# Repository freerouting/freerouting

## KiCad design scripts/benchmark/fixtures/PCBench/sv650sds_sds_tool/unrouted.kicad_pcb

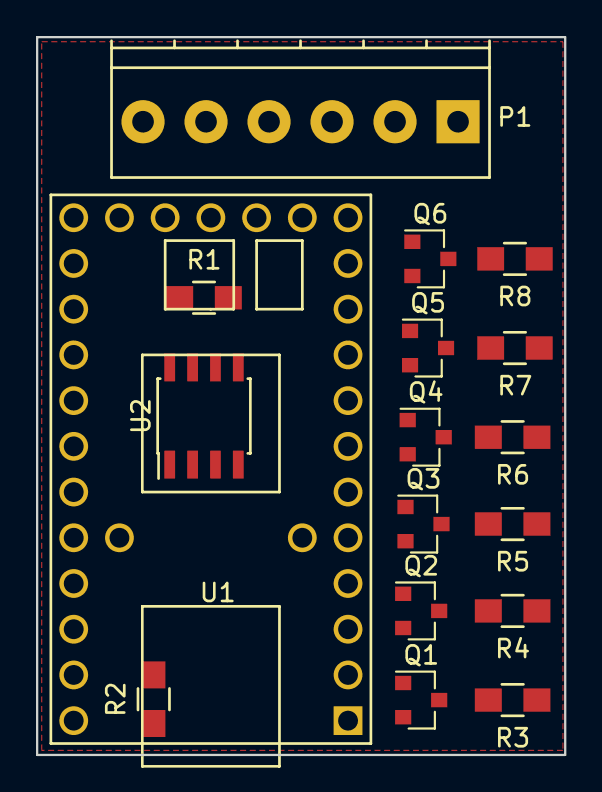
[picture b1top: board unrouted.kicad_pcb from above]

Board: 2 copper layers, 29.3 x 39.9 mm, 17 parts (0 on the bottom side), 21 nets, no tracks yet.

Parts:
P1: CONN_01X06; TerminalBlock_Pheonix_PT-3.5mm_6pol
Q1, Q2, Q3, Q4, Q5, Q6: MMBT3904; SOT-23
R1: 510; R_0805_HandSoldering
R2: 1k; R_0805_HandSoldering
R3: 560; R_0805_HandSoldering
R4: 630; R_0805_HandSoldering
R5: 1.5k; R_0805_HandSoldering
R6: 2.7k; R_0805_HandSoldering
R7: 6.8k; R_0805_HandSoldering
R8: 15k; R_0805_HandSoldering
U1: Teensy2.0
U2: STl9637; SOIC-8_3.9x4.9mm_Pitch1.27mm

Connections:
+5V: R2.1, U1.29, U2.3
+12V: P1.6, R1.1, U2.7
ECU_GPS: P1.2, R3.1, R4.1, R5.1, R6.1, R7.1, R8.1
GND: P1.1, Q1.2, Q2.2, Q3.2, Q4.2, Q5.2, Q6.2, U1.1, U1.15, U2.5
GPS: P1.3, R2.2, U1.28
Gear1: Q1.1, U1.2
Gear2: Q2.1, U1.3
Gear3: Q3.1, U1.4
Gear4: Q4.1, U1.5
Gear5: Q5.1, U1.6
Gear6: Q6.1, U1.7
K_LINE: P1.4, R1.2, U2.6
unnamed: Q1.3, R3.2
unnamed: Q2.3, R4.2
unnamed: Q3.3, R5.2
unnamed: Q4.3, R6.2
unnamed: Q5.3, R7.2
unnamed: Q6.3, R8.2
OUTPUT: P1.5, U1.19
TTL_K_RX: U1.9, U2.1
TTL_K_TX: U1.10, U2.4

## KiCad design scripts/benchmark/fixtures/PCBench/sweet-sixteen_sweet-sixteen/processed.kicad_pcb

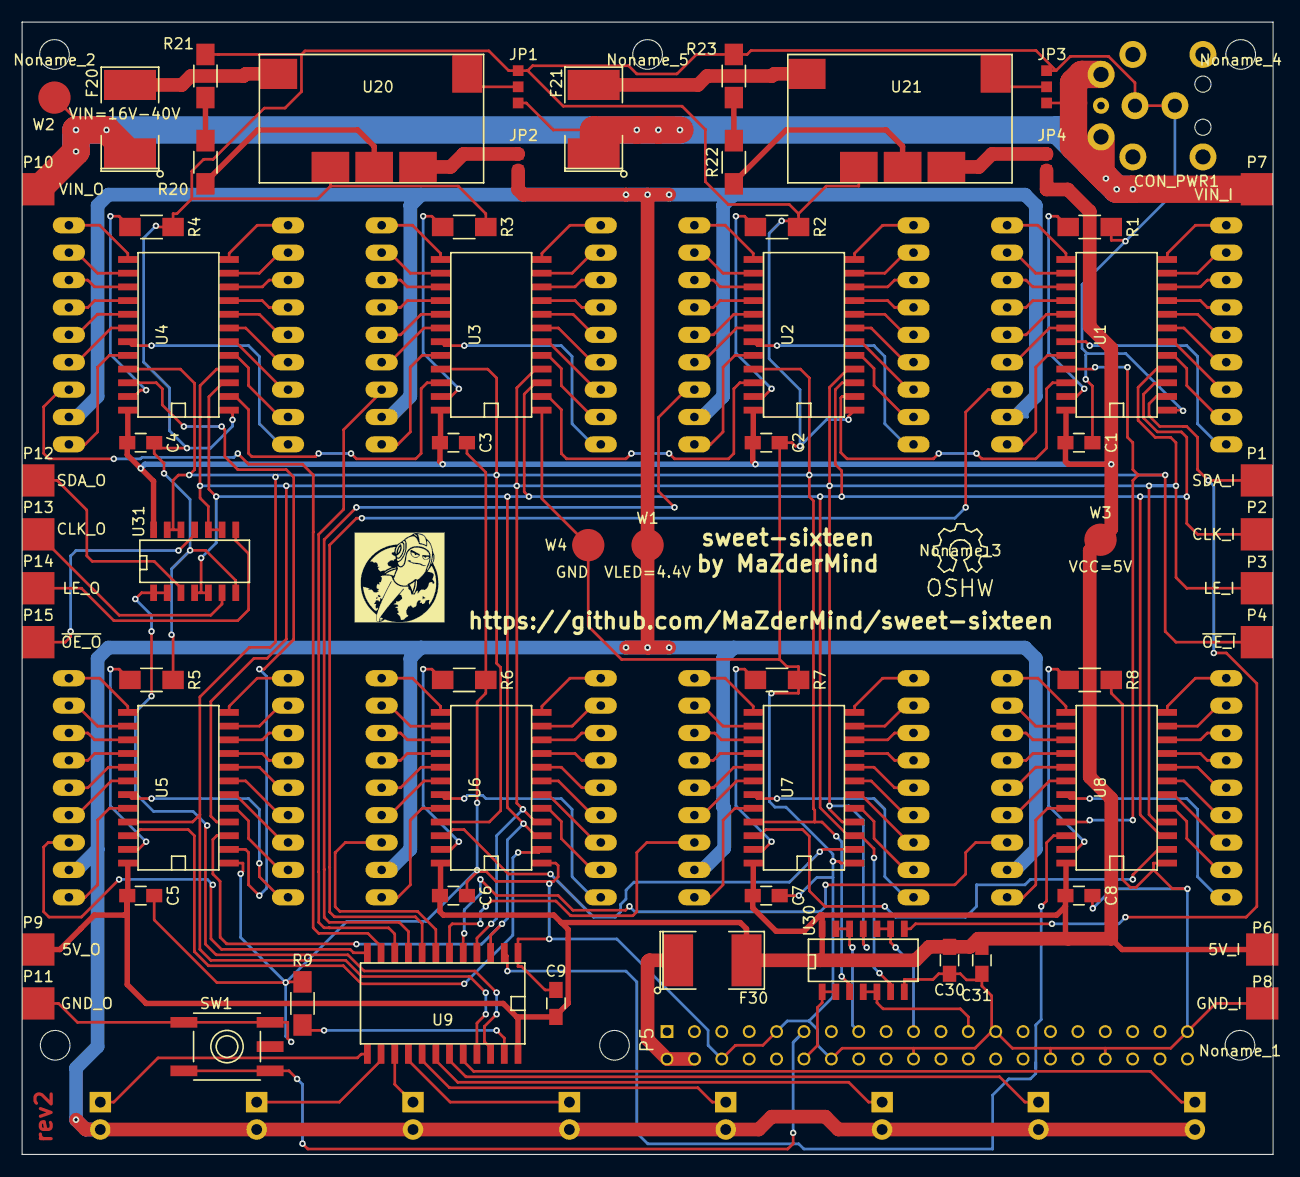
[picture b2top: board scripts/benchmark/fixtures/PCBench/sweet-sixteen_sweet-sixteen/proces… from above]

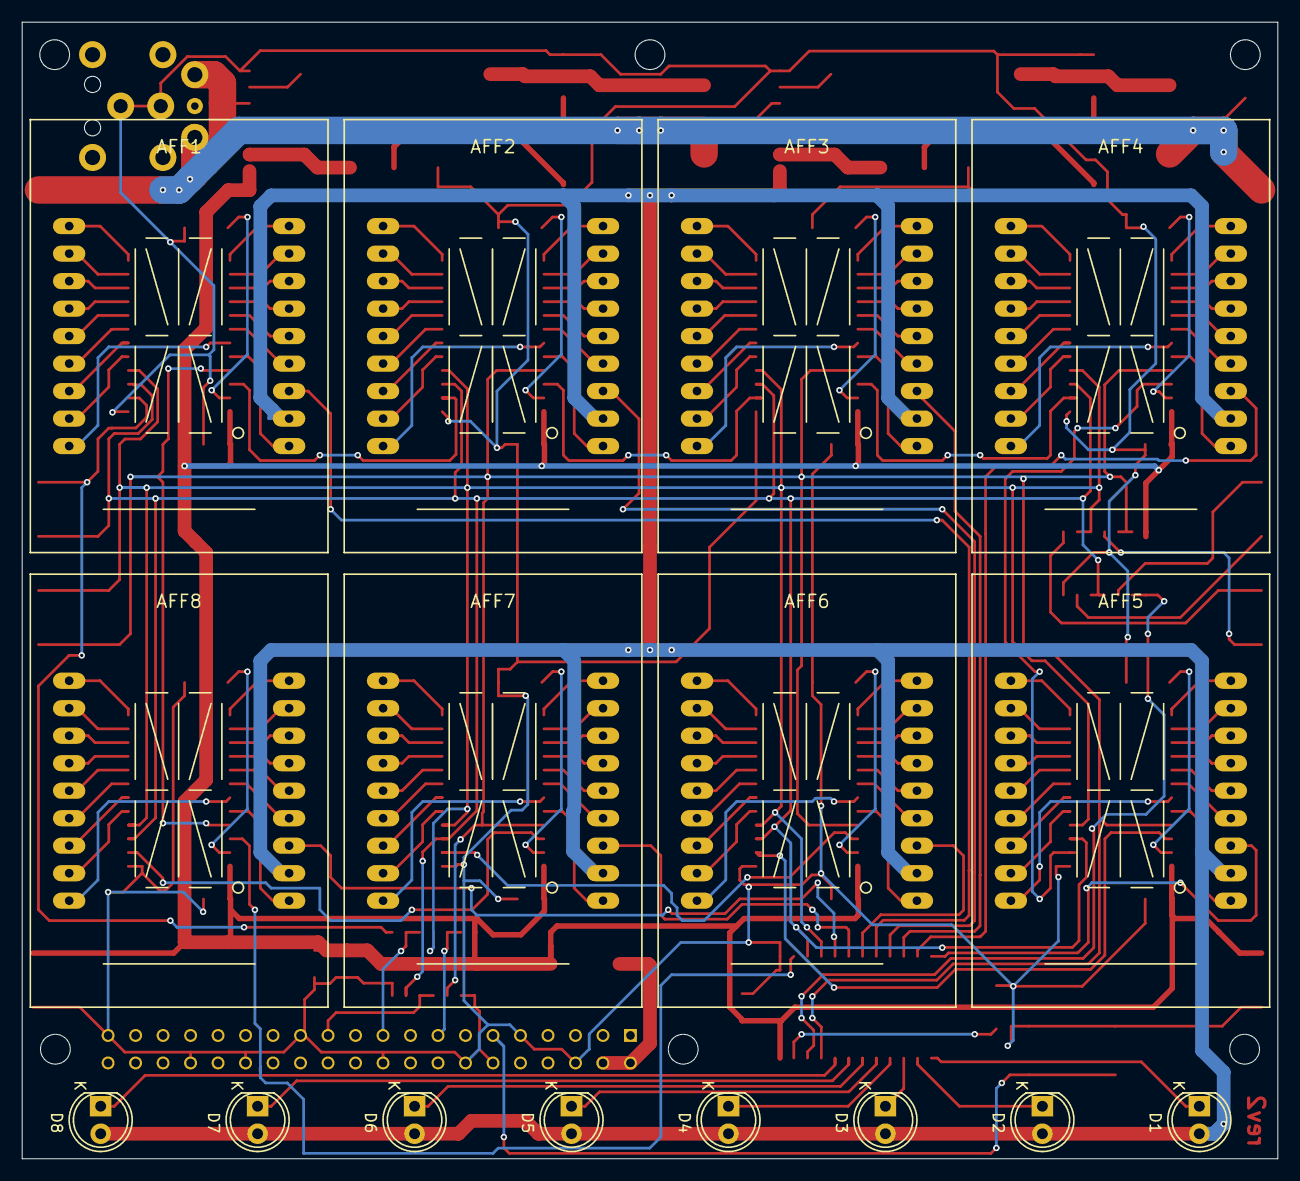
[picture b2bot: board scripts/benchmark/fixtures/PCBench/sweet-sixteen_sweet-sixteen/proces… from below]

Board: 2 copper layers, 116.0 x 105.0 mm, 86 parts (16 on the bottom side), 190 nets.

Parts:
AFF1, AFF2, AFF3, AFF4, AFF5, AFF6, AFF7, AFF8: 16SEGMENTS; PSA12-11
C1, C2, C3, C4, C5, C6, C7, C8, C9, C30, C31: 0.1μF; C_0805_HandSoldering
CON_PWR1: PWR; DELL-PCON
D1, D2, D3, D4, D5, D6, D7, D8: LED; LED-5MM
F20, F21: 1.2A F; SMD-2112_Pol
F30: 2.5A S; SMD-2112_Pol
JP1, JP3: JUMPER3; SMD_Jumper_3
JP2, JP4: JUMPER; SMD_Jumper_2
Noname_1, Noname_2, Noname_4, Noname_5: M2.5; m25-mounting-hole
Noname_3: Symbol_OSHW-Logo_SilkScreen
P1: SDA_I; Measurement_Point_Square-SMD-Pad_Big
P2: CLK_I; Measurement_Point_Square-SMD-Pad_Big
P3: LE_I; Measurement_Point_Square-SMD-Pad_Big
P4: ~OE_I; Measurement_Point_Square-SMD-Pad_Big
P5: CONN_02X20; rpi-header
P6: 5V_I; Measurement_Point_Square-SMD-Pad_Big
P7: VIN_I; Measurement_Point_Square-SMD-Pad_Big
P8: GND_I; Measurement_Point_Square-SMD-Pad_Big
P9: 5V_O; Measurement_Point_Square-SMD-Pad_Big
P10: VIN_O; Measurement_Point_Square-SMD-Pad_Big
P11: GND_O; Measurement_Point_Square-SMD-Pad_Big
P12: SDA_O; Measurement_Point_Square-SMD-Pad_Big
P13: CLK_O; Measurement_Point_Square-SMD-Pad_Big
P14: LE_O; Measurement_Point_Square-SMD-Pad_Big
P15: ~OE_O; Measurement_Point_Square-SMD-Pad_Big
R1, R2, R3, R4, R5, R6, R7, R8, R9: 1k; R_1206_HandSoldering
R20, R22: 1.2k; R_1206_HandSoldering
R21: 680; R_1206_HandSoldering
R23: 270; R_1206_HandSoldering
SW1: SW_PUSH; ADTSM61
U1, U2, U3, U4, U5, U6, U7, U8, U9: STP16CPC26; STP16CPC26MTR
U20, U21: OKI-T/3-W40; OKI-T3
U30, U31: 74HCT08; SN74HCT08D
W1: VLED=4.4V; Measurement_Point_Round-SMD-Pad_Big
W2: VIN=16V-40V; Measurement_Point_Round-SMD-Pad_Big
W3: VCC=5V; Measurement_Point_Round-SMD-Pad_Big
W4: GND; Measurement_Point_Round-SMD-Pad_Big

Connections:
/CLK: P2.1, U1.3, U2.3, U3.3, U4.3, U5.3, U6.3, U7.3, U8.3, U9.3, U30.6, U31.4, U31.5
/CLK_O: P13.1, U31.6
/LE: P3.1, U1.4, U2.4, U3.4, U4.4, U5.4, U6.4, U7.4, U8.4, U9.4, U30.11, U31.9, U31.10
/LE_O: P14.1, U31.8
/PI_CLK: P5.23, U30.4, U30.5
/PI_LE: P5.15, U30.12, U30.13
/PI_SDA: P5.19, U30.9, U30.10
/SDA_9O: U9.22, U31.1, U31.2
/SDA_12: U1.22, U2.2
/SDA_34: U3.22, U4.2
/SDA_45: U4.22, U5.2
/SDA_56: U5.22, U6.2
/SDA_67: U6.22, U7.2
/SDA_78: U7.22, U8.2
/SDA_89: U8.22, U9.2
/SDA_I: P1.1, U1.2, U30.8
/SDA_O: P12.1, U31.3
/SD_23: U2.22, U3.2
/VLED: AFF1.11, AFF2.11, AFF3.11, AFF4.11, AFF5.11, AFF6.11, AFF7.11, AFF8.11, D1.2, D2.2, D3.2, D4.2, D5.2, D6.2, D7.2, D8.2, JP2.2, W1.1
/V_PI: F30.1, P5.2, P5.4
/~OE: P4.1, U1.21, U2.21, U3.21, U4.21, U5.21, U6.21, U7.21, U8.21, U9.21, U30.3, U31.12, U31.13
/~OE_O: P15.1, U31.11
/~PI_OE: P5.12, U30.1, U30.2
GND: C1.2, C2.2, C3.2, C4.2, C5.2, C6.2, C7.2, C8.2, C9.2, C30.2, C31.2, CON_PWR1.2, JP1.1, JP3.1, P5.6, P5.9, P5.14, P5.20, P5.25, P5.30, P5.34, P5.39, P8.1, P11.1, R1.1, R2.1, R3.1, R4.1, R5.1, R6.1, R7.1, R8.1, R9.1, R21.2, R23.2, SW1.1, U1.1, U2.1, U3.1, U4.1, U5.1, U6.1, U7.1, U8.1, U9.1, U20.3, U21.3, U30.7, U31.7, W4.1
unnamed: AFF1.1, U1.12
unnamed: AFF1.2, U1.11
unnamed: AFF1.3, U1.10
unnamed: AFF1.4, U1.9
unnamed: AFF1.5, U1.8
unnamed: AFF1.6, U1.7
unnamed: AFF1.7, U1.6
unnamed: AFF1.8, U1.5
unnamed: AFF1.9, U1.19
unnamed: AFF1.10, U1.20
unnamed: AFF1.12, U9.8
unnamed: AFF1.13, U1.18
unnamed: AFF1.14, U1.17
unnamed: AFF1.15, U1.16
unnamed: AFF1.16, U1.15
unnamed: AFF1.17, U1.14
unnamed: AFF1.18, U1.13
unnamed: AFF2.1, U2.12
unnamed: AFF2.2, U2.11
unnamed: AFF2.3, U2.10
unnamed: AFF2.4, U2.9
unnamed: AFF2.5, U2.8
unnamed: AFF2.6, U2.7
unnamed: AFF2.7, U2.6
unnamed: AFF2.8, U2.5
unnamed: AFF2.9, U2.19
unnamed: AFF2.10, U2.20
unnamed: AFF2.12, U9.9
unnamed: AFF2.13, U2.18
unnamed: AFF2.14, U2.17
unnamed: AFF2.15, U2.16
unnamed: AFF2.16, U2.15
unnamed: AFF2.17, U2.14
unnamed: AFF2.18, U2.13
unnamed: AFF3.1, U3.12
unnamed: AFF3.2, U3.11
unnamed: AFF3.3, U3.10
unnamed: AFF3.4, U3.9
unnamed: AFF3.5, U3.8
unnamed: AFF3.6, U3.7
unnamed: AFF3.7, U3.6
unnamed: AFF3.8, U3.5
unnamed: AFF3.9, U3.19
unnamed: AFF3.10, U3.20
unnamed: AFF3.12, U9.10
unnamed: AFF3.13, U3.18
unnamed: AFF3.14, U3.17
unnamed: AFF3.15, U3.16
unnamed: AFF3.16, U3.15
unnamed: AFF3.17, U3.14
unnamed: AFF3.18, U3.13
unnamed: AFF4.1, U4.12
unnamed: AFF4.2, U4.11
unnamed: AFF4.3, U4.10
unnamed: AFF4.4, U4.9
unnamed: AFF4.5, U4.8
unnamed: AFF4.6, U4.7
unnamed: AFF4.7, U4.6
unnamed: AFF4.8, U4.5
unnamed: AFF4.9, U4.19
unnamed: AFF4.10, U4.20
unnamed: AFF4.12, U9.11
unnamed: AFF4.13, U4.18
unnamed: AFF4.14, U4.17
unnamed: AFF4.15, U4.16
unnamed: AFF4.16, U4.15
unnamed: AFF4.17, U4.14
unnamed: AFF4.18, U4.13
unnamed: AFF5.1, U5.12
unnamed: AFF5.2, U5.11
unnamed: AFF5.3, U5.10
unnamed: AFF5.4, U5.9
unnamed: AFF5.5, U5.8
unnamed: AFF5.6, U5.7
unnamed: AFF5.7, U5.6
unnamed: AFF5.8, U5.5
unnamed: AFF5.9, U5.19
unnamed: AFF5.10, U5.20
unnamed: AFF5.12, U9.12
unnamed: AFF5.13, U5.18
unnamed: AFF5.14, U5.17
unnamed: AFF5.15, U5.16
unnamed: AFF5.16, U5.15
unnamed: AFF5.17, U5.14
unnamed: AFF5.18, U5.13
unnamed: AFF6.1, U6.12
unnamed: AFF6.2, U6.11
unnamed: AFF6.3, U6.10
unnamed: AFF6.4, U6.9
unnamed: AFF6.5, U6.8
unnamed: AFF6.6, U6.7
unnamed: AFF6.7, U6.6
unnamed: AFF6.8, U6.5
unnamed: AFF6.9, U6.19
unnamed: AFF6.10, U6.20
unnamed: AFF6.12, U9.7
unnamed: AFF6.13, U6.18
unnamed: AFF6.14, U6.17
unnamed: AFF6.15, U6.16
unnamed: AFF6.16, U6.15
unnamed: AFF6.17, U6.14
unnamed: AFF6.18, U6.13
unnamed: AFF7.1, U7.12
unnamed: AFF7.2, U7.11
unnamed: AFF7.3, U7.10
unnamed: AFF7.4, U7.9
unnamed: AFF7.5, U7.8
unnamed: AFF7.6, U7.7
unnamed: AFF7.7, U7.6
unnamed: AFF7.8, U7.5
unnamed: AFF7.9, U7.19
unnamed: AFF7.10, U7.20
unnamed: AFF7.12, U9.6
unnamed: AFF7.13, U7.18
unnamed: AFF7.14, U7.17
unnamed: AFF7.15, U7.16
unnamed: AFF7.16, U7.15
unnamed: AFF7.17, U7.14
unnamed: AFF7.18, U7.13
unnamed: AFF8.1, U8.12
unnamed: AFF8.2, U8.11
unnamed: AFF8.3, U8.10
unnamed: AFF8.4, U8.9
unnamed: AFF8.5, U8.8
unnamed: AFF8.6, U8.7
unnamed: AFF8.7, U8.6
unnamed: AFF8.8, U8.5
unnamed: AFF8.9, U8.19
unnamed: AFF8.10, U8.20
unnamed: AFF8.12, U9.5
unnamed: AFF8.13, U8.18
unnamed: AFF8.14, U8.17
unnamed: AFF8.15, U8.16
unnamed: AFF8.16, U8.15
unnamed: AFF8.17, U8.14
unnamed: AFF8.18, U8.13
unnamed: D1.1, U9.13
unnamed: D2.1, U9.14
unnamed: D3.1, U9.15
unnamed: D4.1, U9.16
unnamed: D5.1, U9.17
unnamed: D6.1, U9.18
unnamed: D7.1, U9.19
unnamed: D8.1, U9.20
unnamed: F20.2, U20.2
unnamed: F21.2, U21.2
unnamed: JP1.2, U20.1
unnamed: JP2.1, U20.5
unnamed: JP3.2, U21.1
unnamed: JP4.1, U21.5
unnamed: P5.11, SW1.2
unnamed: R1.2, U1.23
unnamed: R2.2, U2.23
unnamed: R3.2, U3.23
unnamed: R4.2, U4.23
unnamed: R5.2, U5.23
unnamed: R6.2, U6.23
unnamed: R7.2, U7.23
unnamed: R8.2, U8.23
unnamed: R9.2, U9.23
unnamed: R20.1, R21.1
unnamed: R20.2, U20.4
unnamed: R22.1, R23.1
unnamed: R22.2, U21.4
VCC: C1.1, C2.1, C3.1, C4.1, C5.1, C6.1, C7.1, C8.1, C9.1, C30.1, C31.1, F30.2, JP4.2, P6.1, P9.1, U1.24, U2.24, U3.24, U4.24, U5.24, U6.24, U7.24, U8.24, U9.24, U30.14, U31.14, W3.1
VIN: CON_PWR1.1, F20.1, F21.1, JP1.3, JP3.3, P7.1, P10.1, W2.1

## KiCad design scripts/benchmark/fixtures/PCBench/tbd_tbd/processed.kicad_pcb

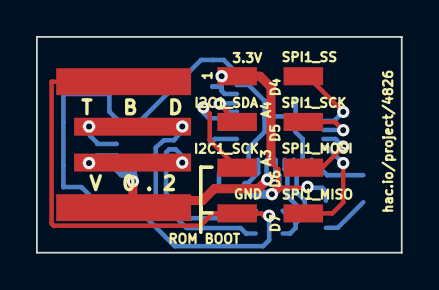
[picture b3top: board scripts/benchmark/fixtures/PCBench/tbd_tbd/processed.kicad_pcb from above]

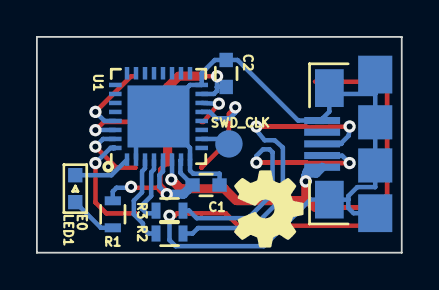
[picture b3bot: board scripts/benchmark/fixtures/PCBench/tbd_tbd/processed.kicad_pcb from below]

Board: 2 copper layers, 20.3 x 12.0 mm, 11 parts (9 on the bottom side), 16 nets.

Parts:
C1, C2: 100nF; C_0603
J1: USBPCB; tbd_USB_A_PCB
J2: USB-MICROB-5PIN; SparkFun-USB-MICROB
LED1: LED0603; LED-0603
P1: CONN_02X04; HEADER_2x4_SMT_RA
R1: 100R; R_0603
R2, R3: 33R; R_0603
SWD_CLK: SWD_CLK; Measurement_Point_Round-SMD-Pad_Small
U1: MKL27ZxxxVFM4; QFN-32-1EP_5x5mm_Pitch0.5mm

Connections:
+3.3V: C1.1, C2.1, P1.1, R1.1, U1.5, U1.7, U1.15
I2C1_SCL: P1.5, U1.13
I2C1_SDA: P1.3, U1.14
unnamed: J1.5V, J2.VBUS, U1.6
unnamed: J1.DN, J2.D-, R3.1
unnamed: J1.DP, J2.D+, R2.1
unnamed: LED1.A, R1.2
unnamed: LED1.C, U1.1
unnamed: R2.2, U1.3
unnamed: R3.2, U1.4
unnamed: SWD_CLK.1, U1.10
SPI1_MISO: P1.8, U1.32
SPI1_MOSI: P1.6, U1.31
SPI1_SCK: P1.4, U1.30
SPI1_SS: P1.2, U1.29
VSS: C1.2, C2.2, J1.GND, J2.GND, J2.MTN1, J2.MTN2, J2.MTN3, J2.MTN4, J2.MTN5, J2.MTN6, P1.7, U1.2, U1.8, U1.16, U1.33

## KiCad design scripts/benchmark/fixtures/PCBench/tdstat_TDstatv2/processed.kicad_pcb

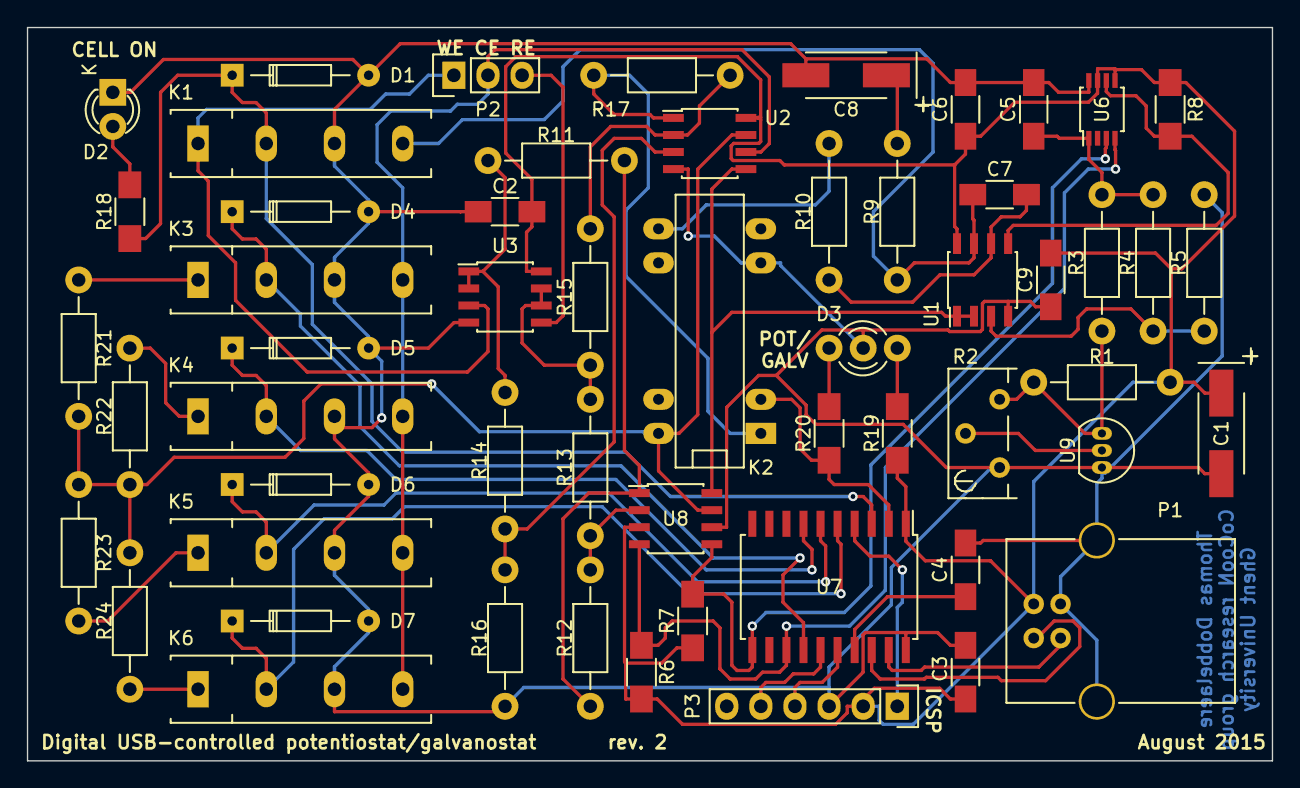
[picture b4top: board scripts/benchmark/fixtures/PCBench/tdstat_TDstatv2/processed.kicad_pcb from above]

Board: 2 copper layers, 92.7 x 54.6 mm, 56 parts (0 on the bottom side), 44 nets.

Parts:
C1, C8: 10 µF; TantalC_SizeC_EIA-6032_HandSoldering
C2, C3, C4, C5, C6, C7, C9: 0.1 µF; C_1206_HandSoldering
D1, D4, D5, D6, D7: 1N4148; Diode_DO-35_SOD27_Horizontal_RM10
D2: CELL ON LED; LED-3MM
D3: MODE LED; DUO-LED-3mm
K1, K3, K4, K5, K6: 9007-05-00; RELAY-9007
K2: HE721C0510; RELAY-HE700
P1: USB_B
P2: CELL_CONN; Pin_Header_Straight_1x03
P3: ICSP_CONN; Pin_Header_Straight_1x06
R1: 1k; Resistor_Horizontal_RM10mm
R2: 10k; Potentiometer_Bourns_3296Y_3-8Zoll_Angular_ScrewUp
R3, R23: 10k 0.1%; Resistor_Horizontal_RM10mm
R4: 18k 0.1%; Resistor_Horizontal_RM10mm
R5: 2k 0.1%; Resistor_Horizontal_RM10mm
R6, R7: 4k7; R_1206_HandSoldering
R8: 100k; R_1206_HandSoldering
R9: 27; Resistor_Horizontal_RM10mm
R10: 100k; Resistor_Horizontal_RM10mm
R11, R12, R13, R22: 1k 0.1%; Resistor_Horizontal_RM10mm
R14, R15: 200k 0.1%; Resistor_Horizontal_RM10mm
R16, R17, R24: 100k 0.1%; Resistor_Horizontal_RM10mm
R18, R19, R20: 1k; R_1206_HandSoldering
R21: 100R 0.1%; Resistor_Horizontal_RM10mm
U1, U2, U3: AD8629; SOIC-8_3.9x4.9mm_Pitch1.27mm
U6: MAX5217; TSSOP-8_3x3mm_Pitch0.65mm
U7: PIC16F1459; SOIC-20_7.5x12.8mm_Pitch1.27mm
U8: MCP3422; SOIC-8_3.9x4.9mm_Pitch1.27mm
U9: TL431; TO-92_Inline_Narrow_Oval

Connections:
+5V: C1.1, C2.1, C3.1, C6.1, C9.1, P1.1, P3.2, R1.2, R6.1, R7.1, R8.2, R19.2, U1.8, U2.8, U3.8, U6.5, U6.7, U7.1, U8.3
/CE: K3.4, K4.4, K5.4, K6.4, P2.2, U2.6
/CELL_ON: D1.1, K1.2, R18.2, U7.3
/D+: P1.3, U7.19
/D-: P1.2, U7.18
/GALV_SENSE+: U1.1, U1.2, U2.5, U8.8
/GALV_SENSE-: K2.14, R21.2, R22.2, R23.2, R24.2, U2.7, U8.7
/ICSPCLK: P3.5, U7.15
/ICSPDAT: P3.4, U7.16
/MCLR: P3.1, U7.4
/MODE_SW: K2.2, R20.2, U7.2
/RANGE1: D4.1, K3.2, U7.14
/RANGE2: D5.1, K4.2, U7.7
/RANGE3: D6.1, K5.2, U7.6
/RANGE4: D7.1, K6.2, U7.5
/RE: P2.3, U3.5
/SCL: R7.2, U6.3, U7.11, U8.5
/SDA: R6.2, U6.4, U7.13, U8.4
/V_REF_2.4V: C5.2, R3.2, R4.2, U6.1
/WE: K1.1, P2.1, U3.3
GND: C1.2, C2.2, C3.2, C4.1, C5.1, C6.2, C8.2, C9.2, D1.2, D2.1, D3.2, D4.2, D5.2, D6.2, D7.2, K1.3, K2.6, K3.3, K4.3, K5.3, K6.3, P1.4, P1.5, P3.3, R2.1, R5.1, R16.2, U1.4, U2.4, U3.4, U6.8, U7.20, U8.6, U9.3
unnamed: C4.2, U7.17
unnamed: C7.1, K1.4, R9.1, U1.7
unnamed: C7.2, R10.2, U1.6
unnamed: C8.1, R9.2
unnamed: D2.2, R18.1
unnamed: D3.1, R19.1
unnamed: D3.3, R20.1
unnamed: K2.1, R17.2, U2.1
unnamed: K2.8, R10.1
unnamed: K3.1, R21.1
unnamed: K4.1, R22.1
unnamed: K5.1, R23.1
unnamed: K6.1, R24.1
unnamed: R1.1, R2.3, R3.1, U9.1
unnamed: R2.2, U9.2
unnamed: R4.1, R5.2, U1.3
unnamed: R8.1, U1.5, U6.6
unnamed: R11.1, R12.2, U8.1
unnamed: R11.2, R14.2, U3.1, U3.2
unnamed: R12.1, R13.2, U8.2
unnamed: R13.1, R15.1, U3.6, U3.7
unnamed: R14.1, R16.1, U2.3
unnamed: R15.2, R17.1, U2.2
